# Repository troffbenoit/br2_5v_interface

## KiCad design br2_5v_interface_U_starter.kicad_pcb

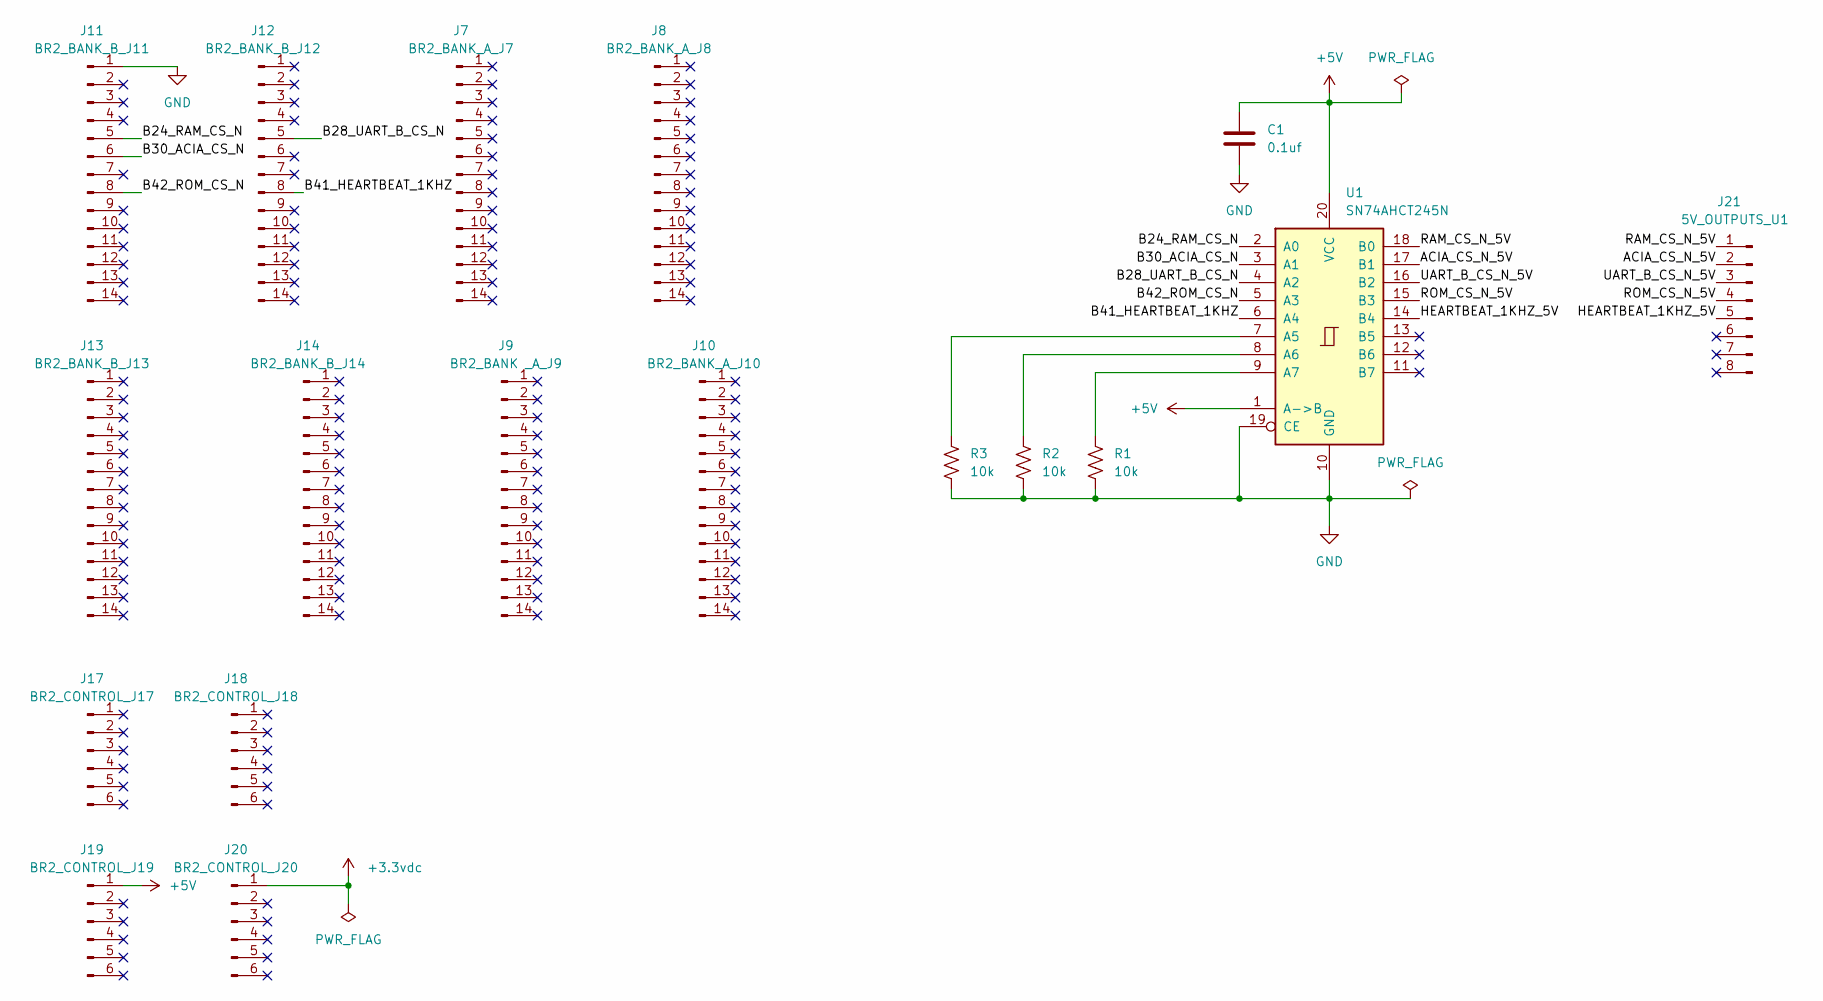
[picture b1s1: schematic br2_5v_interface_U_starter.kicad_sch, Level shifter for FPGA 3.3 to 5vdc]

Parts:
C1: 0.1uf; C_Disc_D5.0mm_W2.5mm_P5.00mm
J7: BR2_BANK_A_J7; PinHeader_1x14_P2.54mm_Vertical
J8: BR2_BANK_A_J8; PinHeader_1x14_P2.54mm_Vertical
J9: BR2_BANK _A_J9; PinHeader_1x14_P2.54mm_Vertical
J10: BR2_BANK_A_J10; PinHeader_1x14_P2.54mm_Vertical
J11: BR2_BANK_B_J11; PinHeader_1x14_P2.54mm_Vertical
J12: BR2_BANK_B_J12; PinHeader_1x14_P2.54mm_Vertical
J13: BR2_BANK_B_J13; PinHeader_1x14_P2.54mm_Vertical
J14: BR2_BANK_B_J14; PinHeader_1x14_P2.54mm_Vertical
J17: BR2_CONTROL_J17; PinHeader_1x06_P2.54mm_Vertical
J18: BR2_CONTROL_J18; PinHeader_1x06_P2.54mm_Vertical
J19: BR2_CONTROL_J19; PinHeader_1x06_P2.54mm_Vertical
J20: BR2_CONTROL_J20; PinHeader_1x06_P2.54mm_Vertical
J21: 5V_OUTPUTS_U1; PinHeader_1x08_P2.54mm_Vertical
R1, R2, R3: 10k; R_Axial_DIN0207_L6.3mm_D2.5mm_P10.16mm_Horizontal
U1: SN74AHCT245N; DIP-20_W7.62mm

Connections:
+3.3vdc: J20.1 (Pin_1_1)
+5V: C1.1, J19.1 (Pin_1_1), U1.1 (A->B), U1.20 (VCC)
/ACIA_CS_N_5V: J21.2, U1.17 (B1)
/B24_RAM_CS_N: J11.5, U1.2 (A0)
/B28_UART_B_CS_N: J12.5, U1.4 (A2)
/B30_ACIA_CS_N: J11.6, U1.3 (A1)
/B41_HEARTBEAT_1KHZ: J12.8, U1.6 (A4)
/B42_ROM_CS_N: J11.8, U1.5 (A3)
/HEARTBEAT_1KHZ_5V: J21.5, U1.14 (B4)
/RAM_CS_N_5V: J21.1, U1.18 (B0)
/ROM_CS_N_5V: J21.4, U1.15 (B3)
/UART_B_CS_N_5V: J21.3, U1.16 (B2)
GND: C1.2, J11.1, R1.1, R2.1, R3.1, U1.10 (GND), U1.19 (CE)
unnamed: R3.2, U1.7 (A5)
unnamed: R2.2, U1.8 (A6)
unnamed: R1.2, U1.9 (A7)

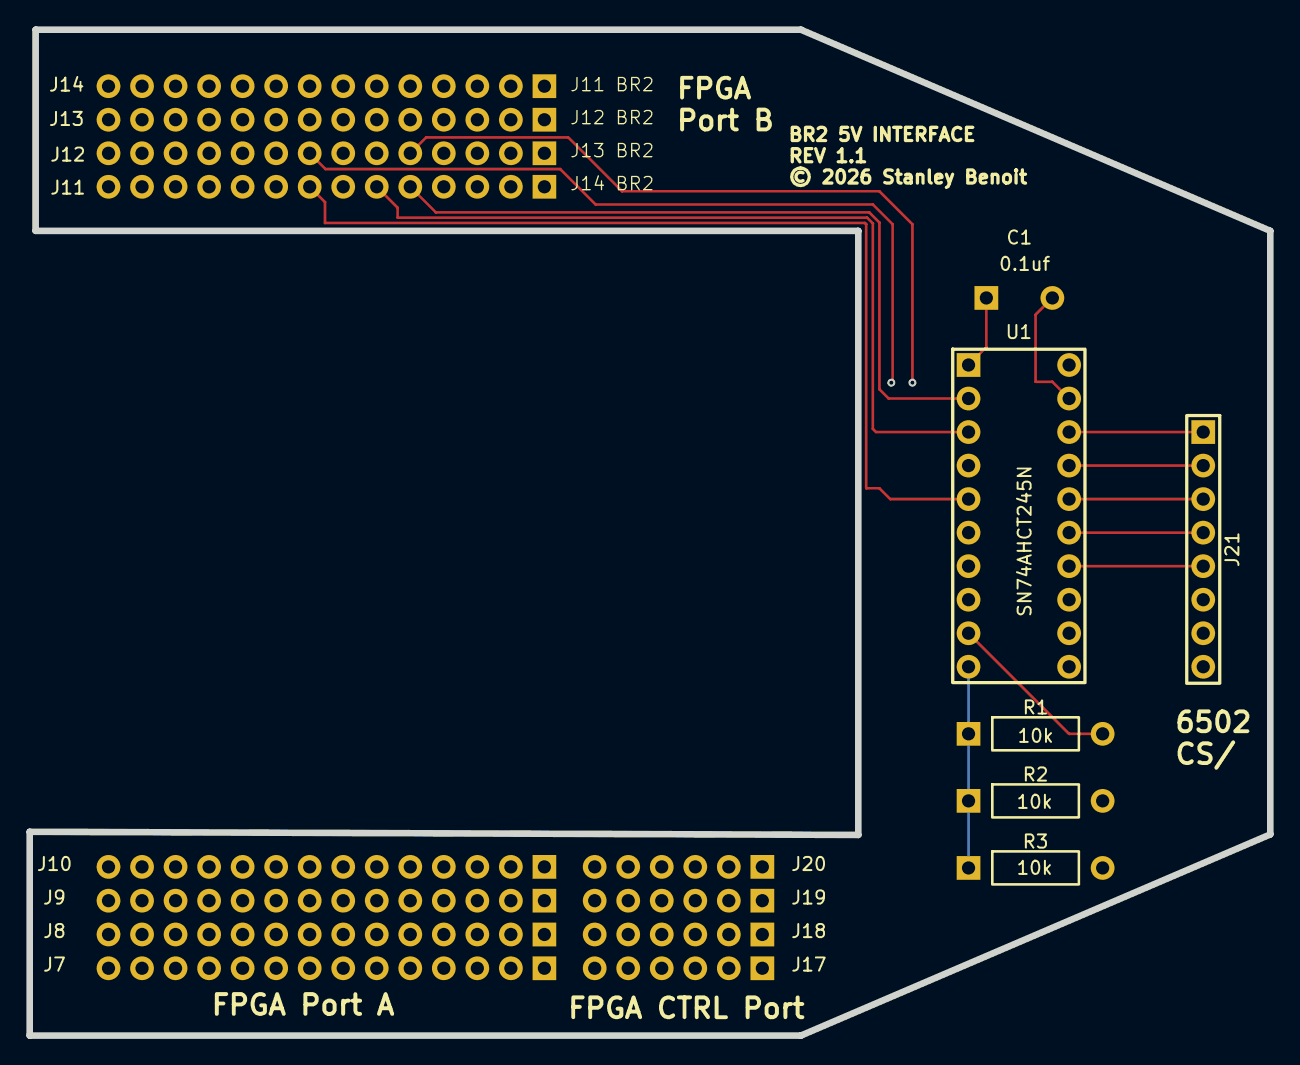
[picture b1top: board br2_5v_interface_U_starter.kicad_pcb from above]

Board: 4 copper layers, 94.0 x 76.2 mm, 18 parts (0 on the bottom side), 15 nets.

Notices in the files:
br2_5v_interface_U_starter.kicad_pcb:
© 2026 Stanley Benoit
